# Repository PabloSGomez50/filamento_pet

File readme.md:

# Proyecto máquina de filamento PET a partir de botellas

## Estructura
- código
El repositorio cuenta con el código que se debe utilizar en el arduino nano
- STLs
Archivos de las piezas que se necesitan imprimir en 3D
- esquemático y pcb

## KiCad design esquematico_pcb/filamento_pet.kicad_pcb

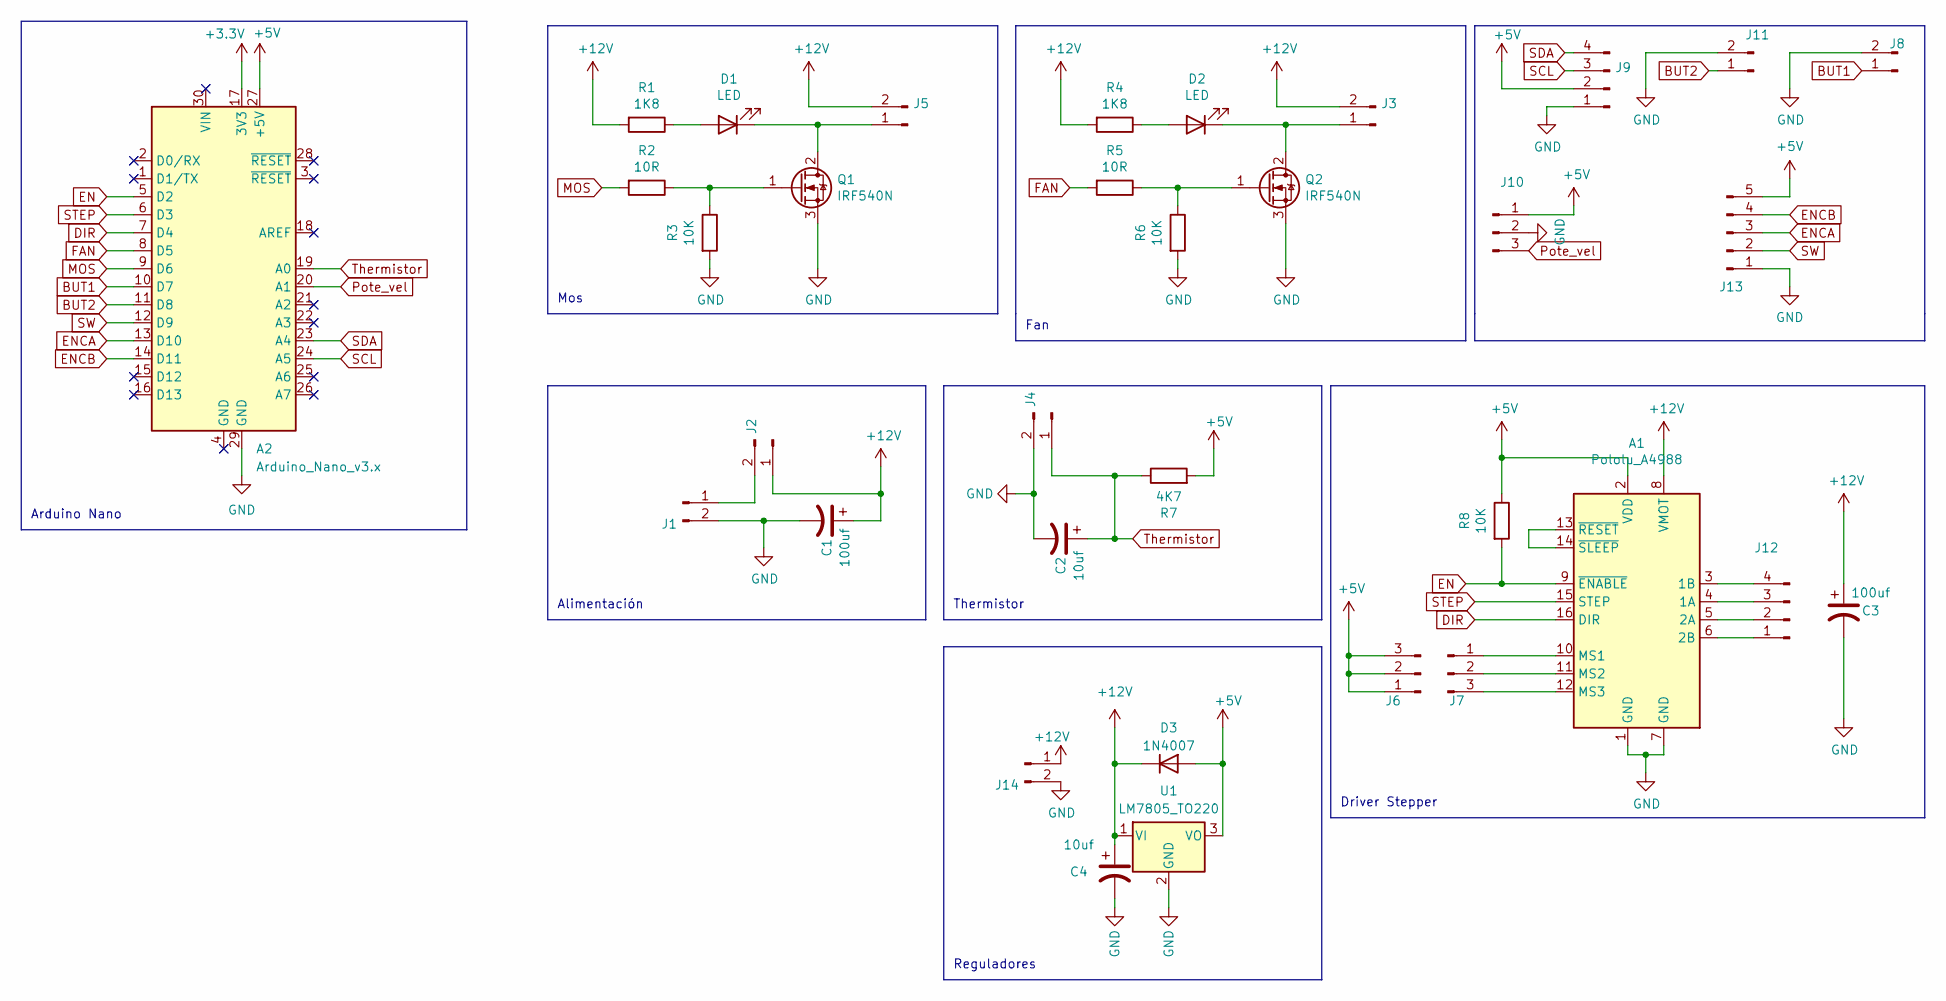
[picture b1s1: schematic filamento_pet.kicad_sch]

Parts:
A1: Pololu_A4988; Pololu_Breakout-16_15.2x20.3mm
A2: Arduino_Nano_v3.x; Arduino_Nano
C1, C3: 100uf; CP_Radial_D8.0mm_P3.50mm
C2, C4: 10uf; CP_Radial_D8.0mm_P3.50mm
D1, D2: LED; LED_D5.0mm
D3: 1N4007; D_DO-41_SOD81_P10.16mm_Horizontal
J1, J2, J3, J4, J5, J8, J11, J14: 01x02M; TerminalBlock_4Ucon_1x02_P3.50mm_Horizontal
J6, J7, J10: 01x03M; PinHeader_1x03_P2.54mm_Vertical
J9, J12: 01x04M; PinHeader_1x04_P2.54mm_Vertical
J13: Conn_01x05_Pin; PinHeader_1x05_P2.54mm_Vertical
Q1, Q2: IRF540N; TO-220-3_Vertical
R1, R4: 1K8; R_Axial_DIN0204_L3.6mm_D1.6mm_P7.62mm_Horizontal
R2, R5: 10R; R_Axial_DIN0204_L3.6mm_D1.6mm_P7.62mm_Horizontal
R3, R6, R8: 10K; R_Axial_DIN0204_L3.6mm_D1.6mm_P7.62mm_Horizontal
R7: 4K7; R_Axial_DIN0204_L3.6mm_D1.6mm_P7.62mm_Horizontal
U1: LM7805_TO220; TO-220-3_Vertical

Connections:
+3.3V: A2.17 (3V3)
+5V: A1.2 (VDD), A2.27 (+5V), D3.2 (A), J6.1, J6.2, J6.3, J9.2, J10.1, J13.5, R7.2, R8.1, U1.3 (VO)
+12V: A1.8 (VMOT), C1.1, C3.1, C4.1, D3.1 (K), J2.1, J3.2, J5.2, J14.1, R1.2, R4.2, U1.1 (VI)
BUT1: A2.10 (D7), J8.1
BUT2: A2.11 (D8), J11.1
DIR: A1.16 (DIR), A2.7 (D4)
EN: A1.9 (~ENABLE), A2.5 (D2), R8.2
ENCA: A2.13 (D10), J13.3
ENCB: A2.14 (D11), J13.4
FAN: A2.8 (D5), R5.2
GND: A1.1 (GND), A1.7 (GND), A2.29 (GND), C1.2, C2.2, C3.2, C4.2, J1.2, J4.2, J8.2, J9.1, J10.2, J11.2, J13.1, J14.2, Q1.3 (S), Q2.3 (S), R3.2, R6.2, U1.2 (GND)
MOS: A2.9 (D6), R2.2
unnamed: A1.4 (1A), J12.3
unnamed: A1.3 (1B), J12.4
unnamed: A1.5 (2A), J12.2
unnamed: A1.6 (2B), J12.1
unnamed: A1.10 (MS1), J7.1
unnamed: A1.11 (MS2), J7.2
unnamed: A1.12 (MS3), J7.3
unnamed: A1.13 (~RESET), A1.14 (~SLEEP)
unnamed: D1.2 (A), R1.1
unnamed: D1.1 (K), J5.1, Q1.2 (D)
unnamed: D2.2 (A), R4.1
unnamed: D2.1 (K), J3.1, Q2.2 (D)
unnamed: J1.1, J2.2
unnamed: Q1.1 (G), R2.1, R3.1
unnamed: Q2.1 (G), R5.1, R6.1
Pote_vel: A2.20 (A1), J10.3
SCL: A2.24 (A5), J9.3
SDA: A2.23 (A4), J9.4
STEP: A1.15 (STEP), A2.6 (D3)
SW: A2.12 (D9), J13.2
Thermistor: A2.19 (A0), C2.1, J4.1, R7.1

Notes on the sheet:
Fan
Driver Stepper
Alimentación
Arduino Nano
Reguladores
Mos
Thermistor

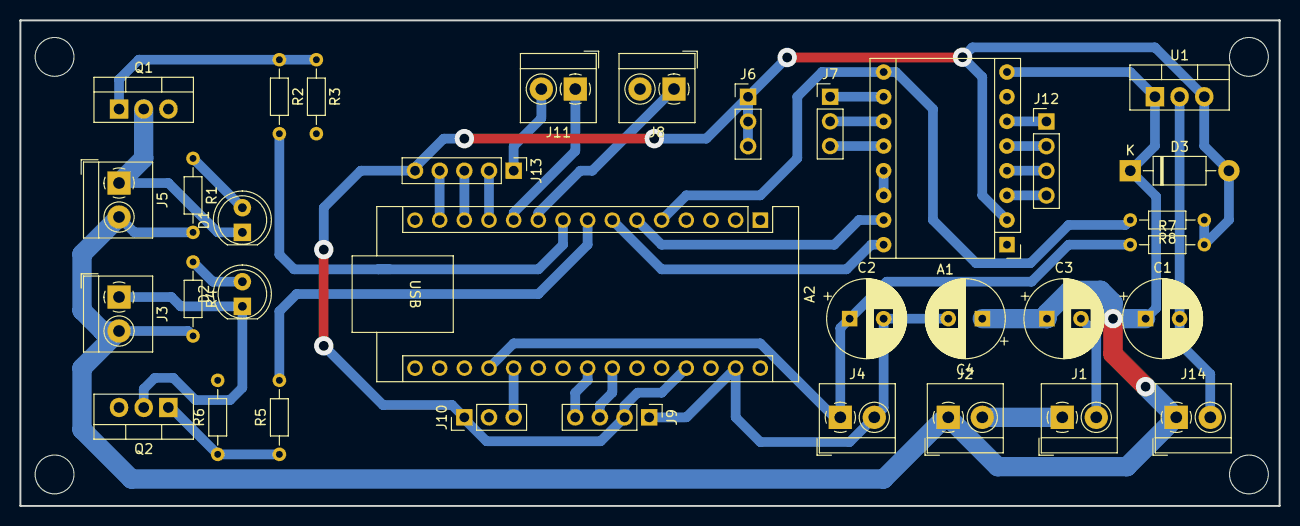
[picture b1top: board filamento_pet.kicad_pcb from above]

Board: 2 copper layers, 129.7 x 50.0 mm, 34 parts (0 on the bottom side), 32 nets.

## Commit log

2023-06-01 Init repositorio: esquematico terminado, falta pcb
2023-06-10 Footprints elegidos
2023-06-11 Footprints listos
2023-06-11 Version sin footprints, necesario para merge
2023-06-11 Cambio de footprint Arduino Nano. Conector para encoder (Opcional). 2 Botones
2023-06-12 PCB V1.0.0
    Agregué LM7805
    Cambios pequeños en el esquemático
    V1.0.0 del PCB
2023-07-15 Cambios recomendados por gonza
    Hice varios cambios, agregué más puntes para que el power plane del GND sea mejor, Gonza comentó de agregar resistencias de pull down en las entradas de MSI del pololu, estas eran para controlar el s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
